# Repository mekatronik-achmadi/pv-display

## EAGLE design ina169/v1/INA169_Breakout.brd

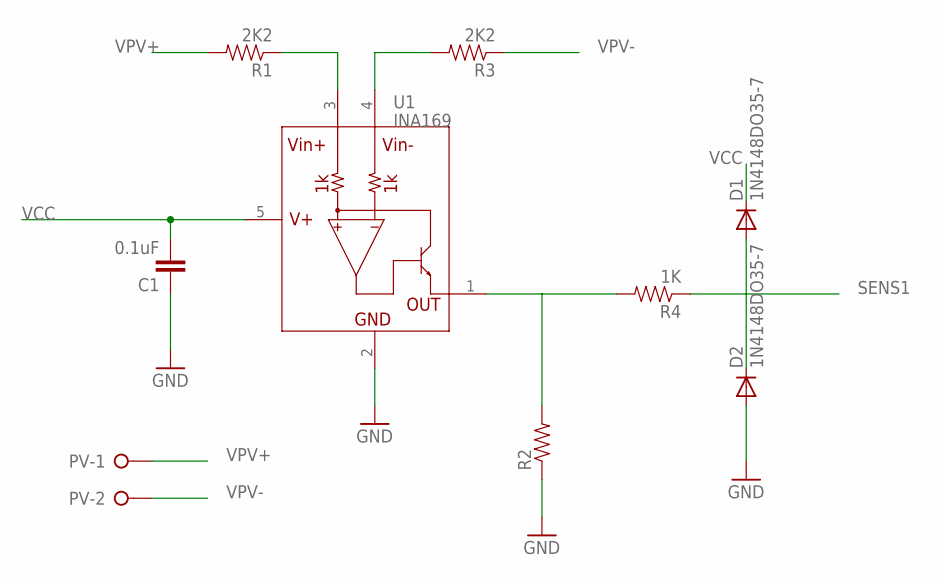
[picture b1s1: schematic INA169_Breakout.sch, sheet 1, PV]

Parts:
C1: 0.1uF; 0603-CAP
D1, D2: 1N4148DO35-7; DO35-7
PV: W237-02P; W237-132
R1, R3: 2K2; 0603-RES
R2: RESISTOR0603; 0603-RES
R4: 1K; 0603-RES
U1: INA169; SOT23-5

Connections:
GND: C1.1, D2.A, R2.1, U1.2 (GND); also elsewhere on the board
unnamed: R3.2, U1.4 (VIN-)
unnamed: R1.1, U1.3 (VIN+)
unnamed: R2.2, R4.2, U1.1 (OUT)
SENS1: D1.A, D2.C, R4.1; also elsewhere on the board
VCC: C1.2, D1.C, U1.5 (V+); also elsewhere on the board
VPV+: PV.1, R1.2
VPV-: PV.2, R3.1

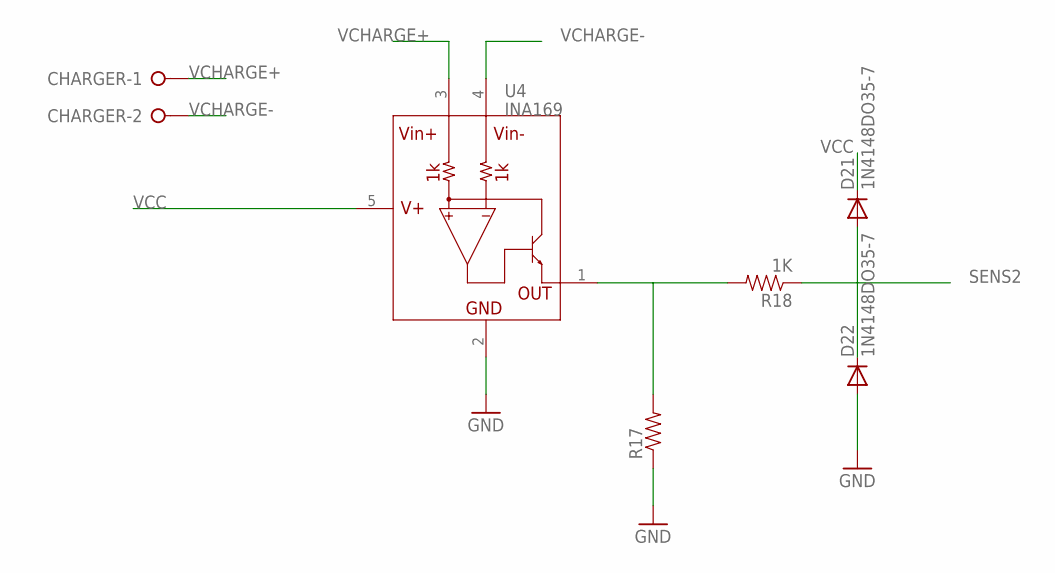
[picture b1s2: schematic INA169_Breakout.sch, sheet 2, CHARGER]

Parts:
CHARGER: W237-02P; W237-132
D21, D22: 1N4148DO35-7; DO35-7
R17: RESISTOR0603; 0603-RES
R18: 1K; 0603-RES
U4: INA169; SOT23-5

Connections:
GND: D22.A, R17.1, U4.2 (GND); also elsewhere on the board
unnamed: R17.2, R18.2, U4.1 (OUT)
SENS2: D21.A, D22.C, R18.1; also elsewhere on the board
VCC: D21.C, U4.5 (V+); also elsewhere on the board
VCHARGE+: CHARGER.1, U4.3 (VIN+)
VCHARGE-: CHARGER.2, U4.4 (VIN-)

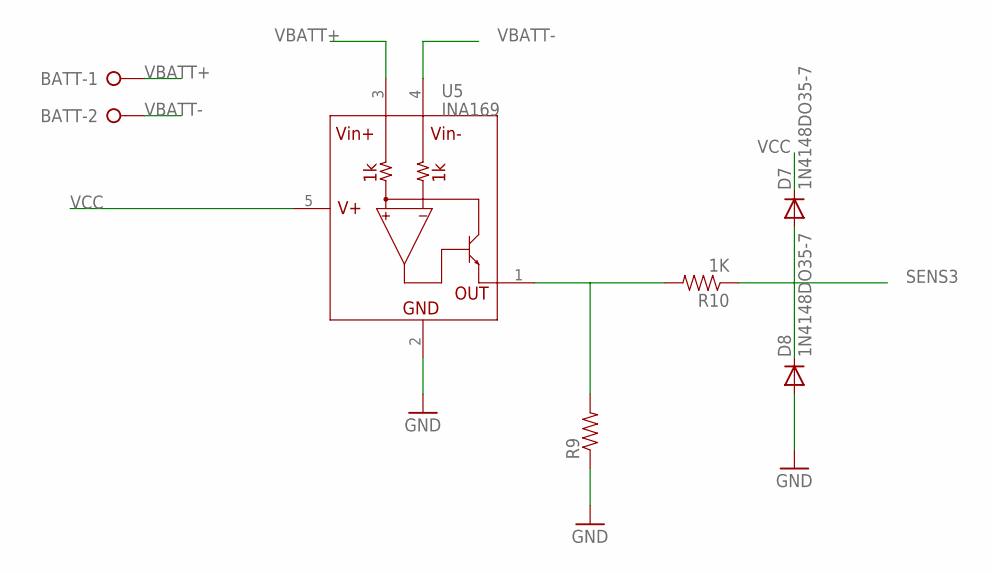
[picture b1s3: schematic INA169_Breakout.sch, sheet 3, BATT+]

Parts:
BATT: W237-02P; W237-132
D7, D8: 1N4148DO35-7; DO35-7
R9: RESISTOR0603; 0603-RES
R10: 1K; 0603-RES
U5: INA169; SOT23-5

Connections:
GND: D8.A, R9.1, U5.2 (GND); also elsewhere on the board
unnamed: R9.2, R10.2, U5.1 (OUT)
SENS3: D7.A, D8.C, R10.1; also elsewhere on the board
VBATT+: BATT.1, U5.3 (VIN+); also elsewhere on the board
VBATT-: BATT.2, U5.4 (VIN-); also elsewhere on the board
VCC: D7.C, U5.5 (V+); also elsewhere on the board

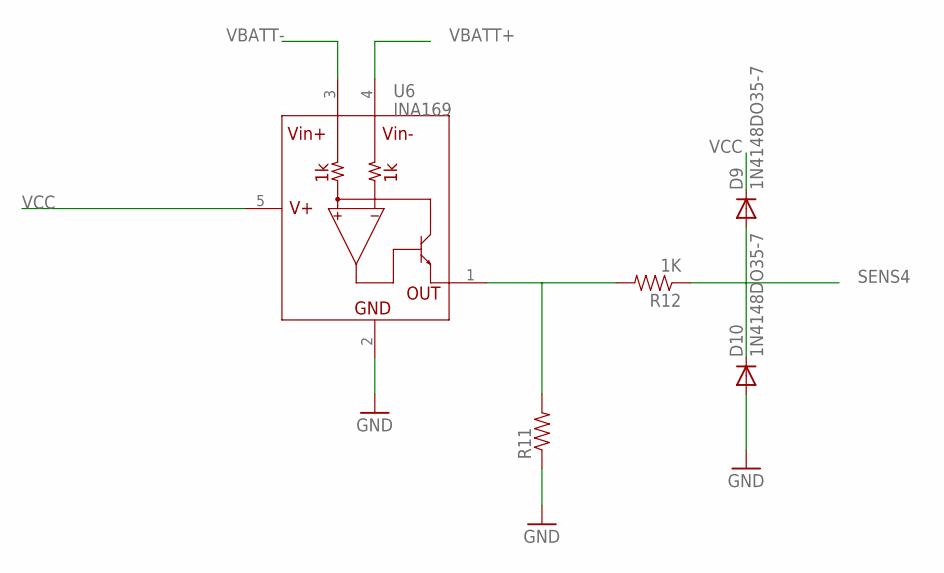
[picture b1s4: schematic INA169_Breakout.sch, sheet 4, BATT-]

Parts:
D9, D10: 1N4148DO35-7; DO35-7
R11: RESISTOR0603; 0603-RES
R12: 1K; 0603-RES
U6: INA169; SOT23-5

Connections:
GND: D10.A, R11.1, U6.2 (GND); also elsewhere on the board
unnamed: R11.2, R12.2, U6.1 (OUT)
SENS4: D9.A, D10.C, R12.1; also elsewhere on the board
VBATT+: U6.4 (VIN-); also elsewhere on the board
VBATT-: U6.3 (VIN+); also elsewhere on the board
VCC: D9.C, U6.5 (V+); also elsewhere on the board

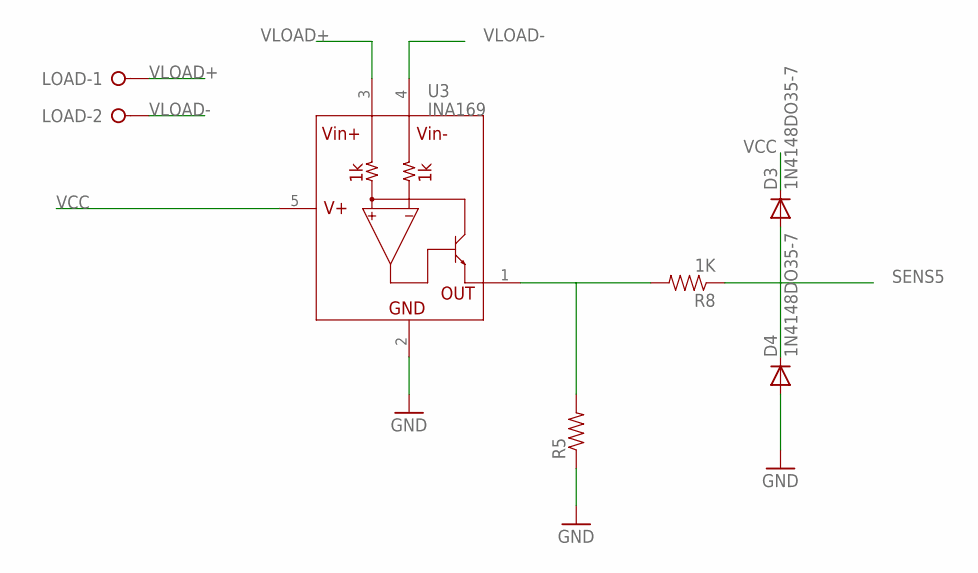
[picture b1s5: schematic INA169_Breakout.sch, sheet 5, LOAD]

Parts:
D3, D4: 1N4148DO35-7; DO35-7
LOAD: W237-02P; W237-132
R5: RESISTOR0603; 0603-RES
R8: 1K; 0603-RES
U3: INA169; SOT23-5

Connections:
GND: D4.A, R5.1, U3.2 (GND); also elsewhere on the board
unnamed: R5.2, R8.2, U3.1 (OUT)
SENS5: D3.A, D4.C, R8.1; also elsewhere on the board
VCC: D3.C, U3.5 (V+); also elsewhere on the board
VLOAD+: LOAD.1, U3.3 (VIN+)
VLOAD-: LOAD.2, U3.4 (VIN-)

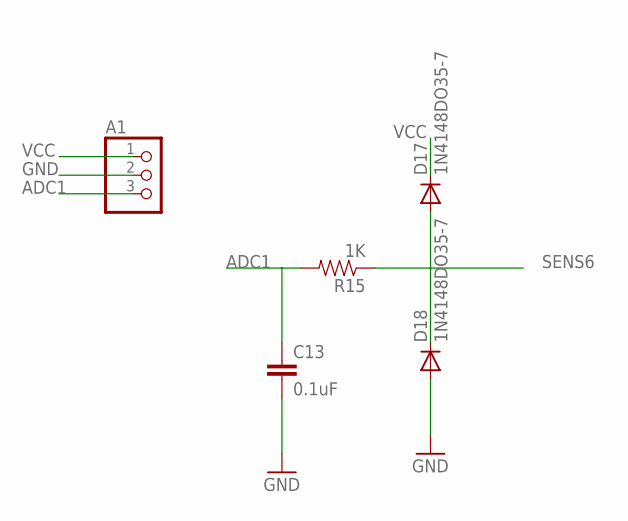
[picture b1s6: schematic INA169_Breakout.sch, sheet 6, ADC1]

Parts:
A1: PINHD-1X3; 1X03
C13: 0.1uF; 0603-CAP
D17, D18: 1N4148DO35-7; DO35-7
R15: 1K; 0603-RES

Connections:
ADC1: A1.3, C13.1, R15.2
GND: A1.2, C13.2, D18.A; also elsewhere on the board
SENS6: D17.A, D18.C, R15.1; also elsewhere on the board
VCC: A1.1, D17.C; also elsewhere on the board

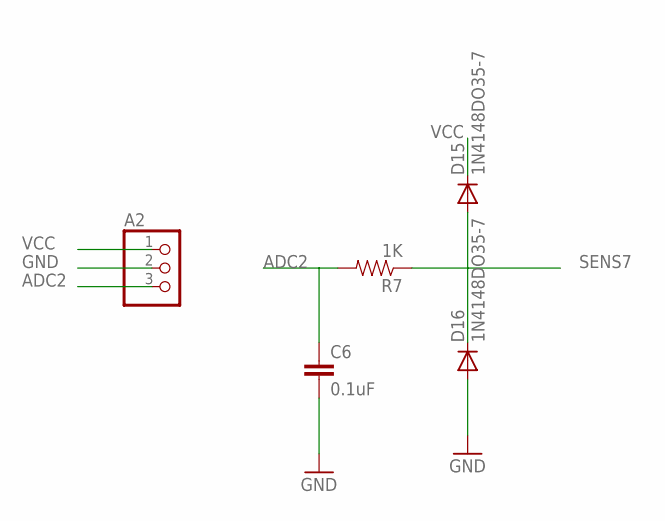
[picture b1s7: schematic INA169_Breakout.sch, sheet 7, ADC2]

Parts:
A2: PINHD-1X3; 1X03
C6: 0.1uF; 0603-CAP
D15, D16: 1N4148DO35-7; DO35-7
R7: 1K; 0603-RES

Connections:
ADC2: A2.3, C6.1, R7.2
GND: A2.2, C6.2, D16.A; also elsewhere on the board
SENS7: D15.A, D16.C, R7.1; also elsewhere on the board
VCC: A2.1, D15.C; also elsewhere on the board

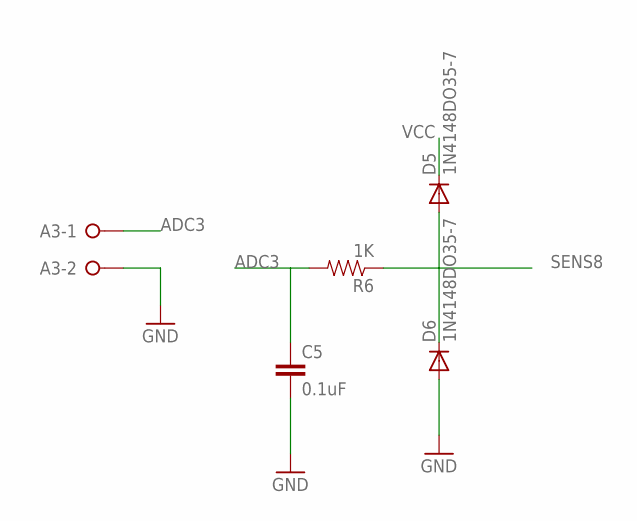
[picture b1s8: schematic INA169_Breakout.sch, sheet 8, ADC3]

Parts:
A3: W237-02P; W237-132
C5: 0.1uF; 0603-CAP
D5, D6: 1N4148DO35-7; DO35-7
R6: 1K; 0603-RES

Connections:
ADC3: A3.1, C5.1, R6.2
GND: A3.2, C5.2, D6.A; also elsewhere on the board
SENS8: D5.A, D6.C, R6.1; also elsewhere on the board
VCC: D5.C; also elsewhere on the board

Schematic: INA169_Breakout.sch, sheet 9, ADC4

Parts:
A4: W237-02P; W237-132
C12: 0.1uF; 0603-CAP
D13, D14: 1N4148DO35-7; DO35-7
R14: 1K; 0603-RES

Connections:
ADC4: A4.1, C12.1, R14.2
GND: A4.2, C12.2, D14.A; also elsewhere on the board
SENS9: D13.A, D14.C, R14.1; also elsewhere on the board
VCC: D13.C; also elsewhere on the board

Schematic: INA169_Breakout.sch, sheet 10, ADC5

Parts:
A5: W237-02P; W237-132
C11: 0.1uF; 0603-CAP
D11, D12: 1N4148DO35-7; DO35-7
R13: 1K; 0603-RES

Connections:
ADC5: A5.1, C11.1, R13.2
GND: A5.2, C11.2, D12.A; also elsewhere on the board
SENS10: D11.A, D12.C, R13.1; also elsewhere on the board
VCC: D11.C; also elsewhere on the board

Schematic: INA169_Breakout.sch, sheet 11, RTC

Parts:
RTC: PINHD-1X4/90; 1X04/90

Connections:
GND: RTC.1; also elsewhere on the board
SCL: RTC.4; also elsewhere on the board
SDA: RTC.3; also elsewhere on the board
VCC: RTC.2; also elsewhere on the board

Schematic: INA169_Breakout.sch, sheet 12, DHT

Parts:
DHT: PINHD-1X3; 1X03

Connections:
D1: DHT.3; also elsewhere on the board
GND: DHT.2; also elsewhere on the board
VCC: DHT.1; also elsewhere on the board

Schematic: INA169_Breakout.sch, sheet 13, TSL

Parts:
TSL: PINHD-1X3; 1X03

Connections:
D2: TSL.3; also elsewhere on the board
GND: TSL.2; also elsewhere on the board
VCC: TSL.1; also elsewhere on the board

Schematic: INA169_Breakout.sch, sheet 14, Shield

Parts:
ANALOG: PINHD-1X6B; 1X06-BIG
DIGITAL1: PINHD-1X8BIG; 1X08-BIG
DIGITAL2: PINHD-1X10; 1X10-BIG
POWER: PINHD-1X8BIG; 1X08-BIG

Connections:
D1: DIGITAL1.5; also elsewhere on the board
D2: DIGITAL1.6; also elsewhere on the board
GND: POWER.6, POWER.7; also elsewhere on the board
SCL: DIGITAL2.10; also elsewhere on the board
SDA: DIGITAL2.9; also elsewhere on the board
SENS1: ANALOG.1; also elsewhere on the board
SENS2: ANALOG.2; also elsewhere on the board
SENS3: ANALOG.3; also elsewhere on the board
SENS4: ANALOG.4; also elsewhere on the board
SENS5: ANALOG.5; also elsewhere on the board
SENS6: DIGITAL1.7; also elsewhere on the board
SENS7: DIGITAL2.1; also elsewhere on the board
SENS8: DIGITAL2.2; also elsewhere on the board
SENS9: DIGITAL2.3; also elsewhere on the board
SENS10: DIGITAL2.5; also elsewhere on the board
VCC: POWER.5; also elsewhere on the board

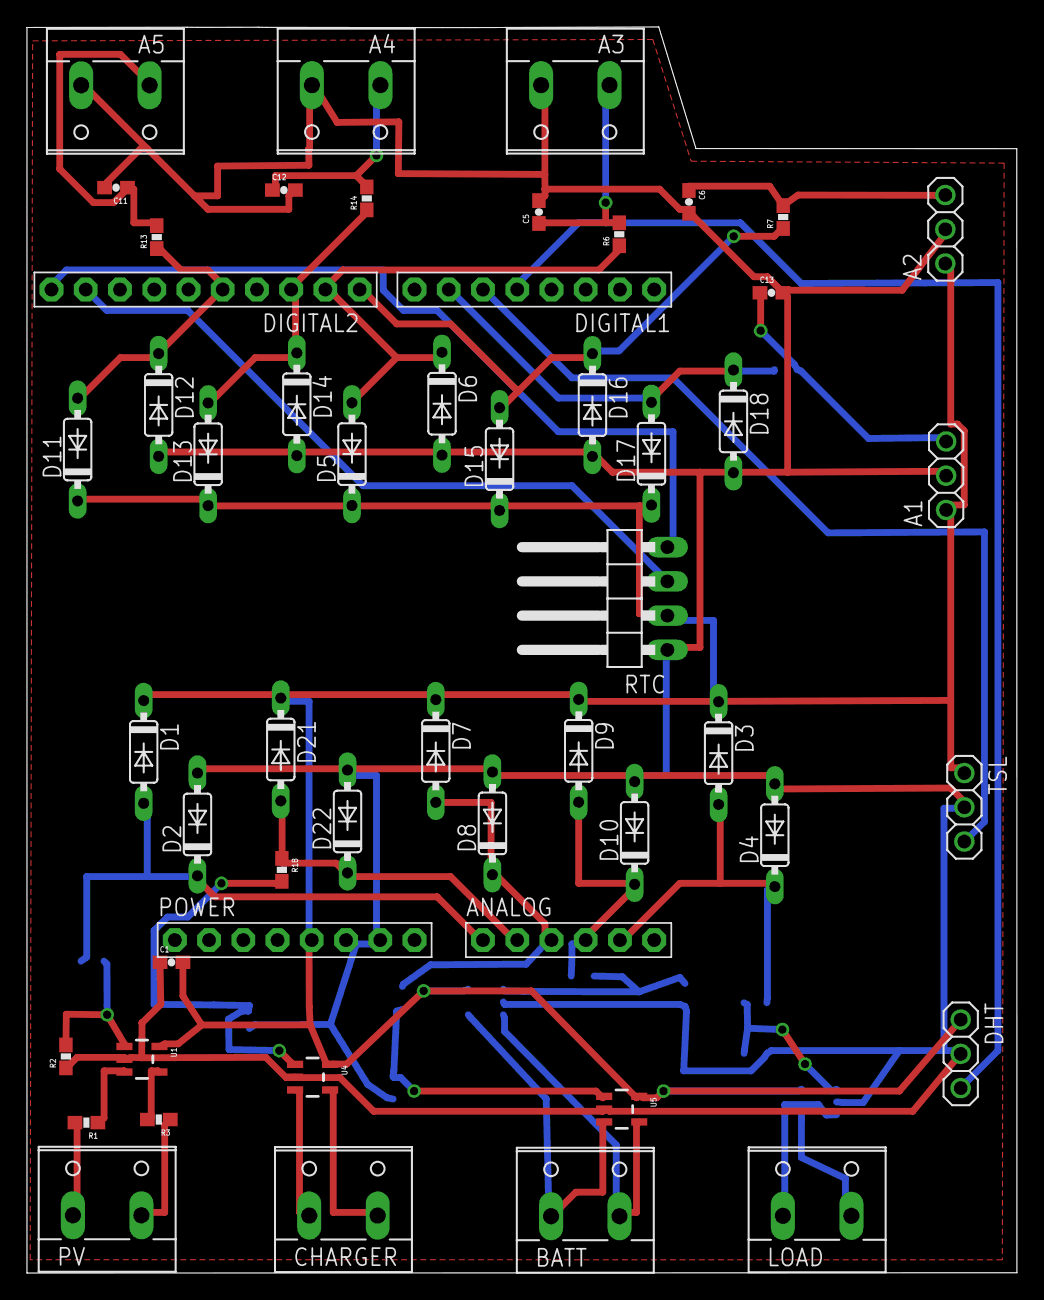
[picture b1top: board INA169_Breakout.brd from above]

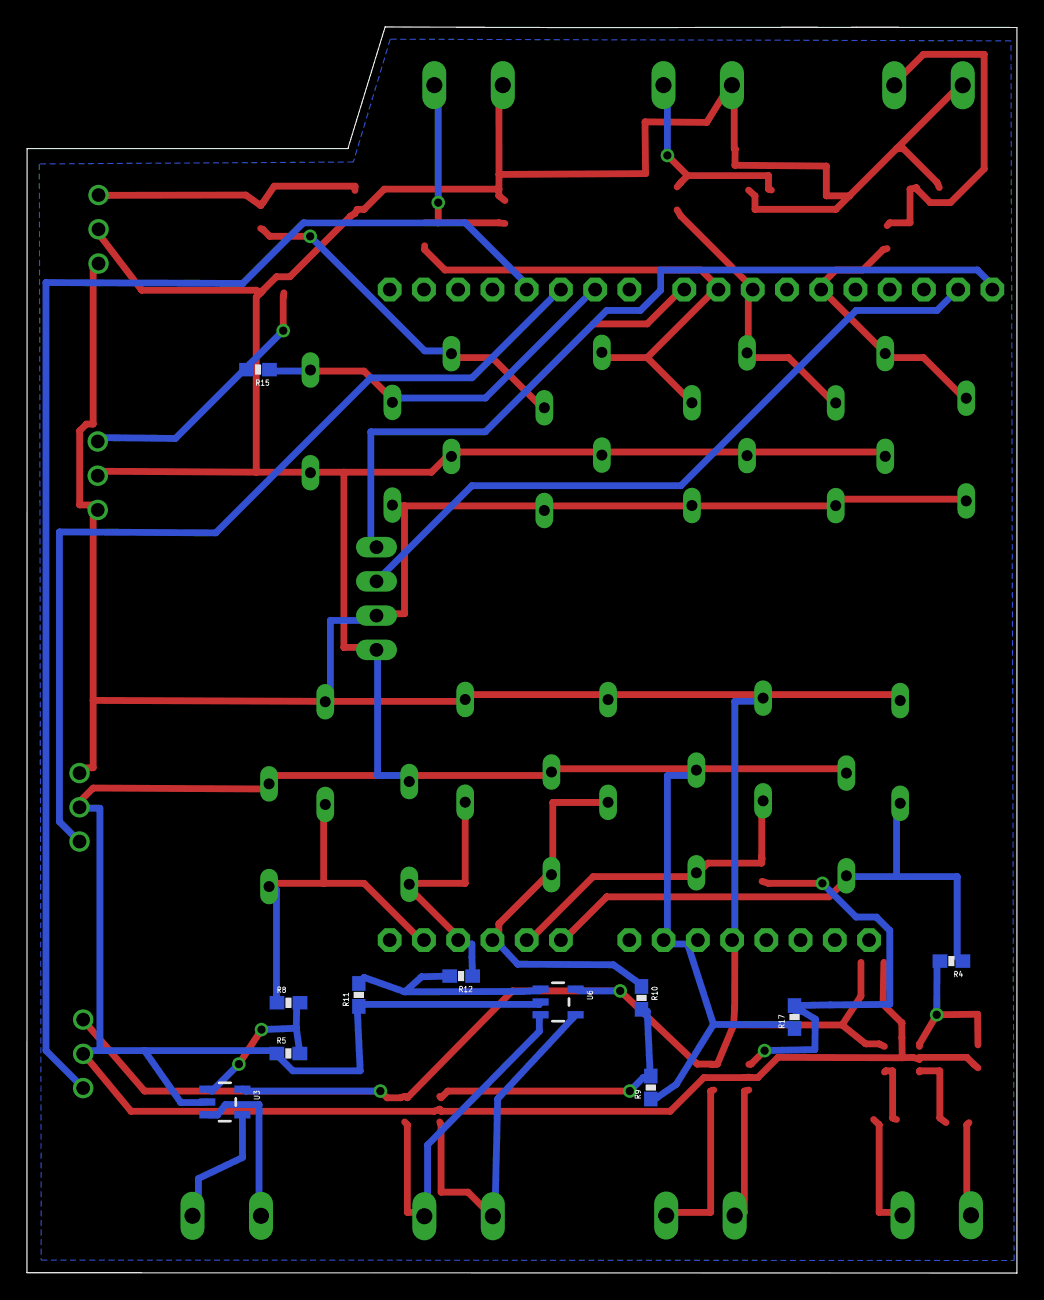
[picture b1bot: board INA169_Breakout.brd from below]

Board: 2 copper layers, 73.4 x 92.4 mm, 64 parts (11 on the bottom side), 36 nets.

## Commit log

2016-05-15 1 inch date board
2016-08-12 development
2016-08-22 finish

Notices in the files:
parts and their libraries:
SparkFun-AnalogIC: Licensing: CC v3.0 Share-Alike You are welcome to use this library for commercial purposes.
